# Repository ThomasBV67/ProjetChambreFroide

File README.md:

# ProjetChambreFroide
## Résumé du projet
Ce répertoire github contient tous les fichiers en lien avec notre projet. Ce projet se résume en un système de mesures et mise en mémoire de températures. Un module principal affiche les températures mesurée, garde en mémoire cette information et permet d'avoir accès à un historique des températures enregistrées. Un nombre variable de modules de mesures envoie des trames LoRa, contenant les températures mesurées par les capteurs de températures connectés à ceux-ci, au module principal.

## Dossiers
#### Électrique
Contient tout les fichiers et dossiers en lien avec la partie électronique du projet.

#### getAdressesCapteurs
Contient le projet arduino de test unitaire pour obtenir l'adresse des capteurs de températures.

#### LoRaSender
Contient le projet arduino de test unitaire d'envoi de trames LoRa.

#### ProgrammeModulesCentraux
Contient le projet arduino utilisé dans les modules de capteurs.

#### ProgrammePontLoRa
Contient le projet arduino utilisé pour faire le pont entre les trames LoRa et la connection série avec l'ordinateur.

#### testCapteurs
Contient le projet arduino utilisé pour tester le concept du projet (obtient les températures et envoi) du côté arduino.

#### TestPi
Contient le projet Visual Studio utilisé pour tester les fonctionnalitées de Windows 10 IoT Core.

#### TestRecieve
Contient le projet arduino utilisé pour tester la réception de trames LoRa.

#### TestSender
Contient le projet arduino utilisé pour tester l'envoi de trames LoRa.

#### UI_ChambreFroide_V1
Contient le projet principal Visual Studio.

## Fichiers
#### System.Data.SQLite.dll
Librairie utilisée pour utiliser SQLite dans le programme principal.

#### firstDraftUI_Projet.png
Idée de base pour l'affichage des températures

## Installation
#### Programme des cartes
Avant de mettre le programme spécifique à une carte, le bootloader doit etre installé. [Comment installer un bootloader](https://support.arduino.cc/hc/en-us/articles/360012048100-How-to-burn-the-bootloader-in-an-Arduino-Nano-using-an-Arduino-UNO)
Avant d'installer le bootloader, assurez vous que les jumpers JP101 et JP102 sont ouverts. Assurez vous de les fermer après son installation.
##### Module pont
Le programme du module pont est disponible sous /ProgrammePontLoRa/ProgrammePontLoRa.ino
Le fichier doit etre ouvert avec le logiciel Arduino.
Le programme est fait pour fonctionner avec les cartes "Module" disponibles sous /Électrique/Module Central/Module Central.pro
Compilez et envoyez le programme à la carte avec le logiciel Arduino
S'assurer que les syncWord des modules LoRa des modules correspondent (Disponibles entre 0x00 et 0xFF)
```c++
LoRa.setSyncWord(0x45);
```
##### Modules centraux
Le programme des modules centraux est disponible sous /ProgrammeModulesCentraux/ProgrammeModulesCentraux.ino
Le fichier doit etre ouvert avec le logiciel Arduino.
Le programme est fait pour fonctionner avec les cartes "Module" disponibles sous /Électrique/Module Central/Module Central.pro
Les cartes doivent etres numérotés. Il faut modifier la constante "NUM_MODULE" en commençant par 1 et en augmentant de 1 pour chaque module prévu sur le réseau
S'assurer que les syncWord des modules LoRa des modules correspondent (Disponibles entre 0x00 et 0xFF)
```c++
LoRa.setSyncWord(0x45);
```
Compilez et envoyez le programme à la carte avec le logiciel Arduino

#### Programme Principal
L'ensemble du programme principal est disponible sous /UI_ChambreFroide_V1/UI_ChambreFroide_V1/
Le projet s'ouvre avec visual studio. S'assurer que l'extensions "Développement .net Desktop" est installée dans VS

## Utilisation
### Commandes
Les commandes sont tout d'abord envoyés à partir d'un ordinateur vers le module de transmission qui se charge d'envoyer les informations de série vers LoRa et vice-versa. La commande est ensuite envoyée en LoRa et est reçue par tous les modules. Les modules vérifient ensuite l'information pour savoir si elle leur est destinée. Elle sera destinée à un seul module. Le module concerné traite ensuite la commande et récupère les informations demandés auprès des capteurs. Il renvois ensuite en un ou plusieurs messages dépendamment de la nature de la commande originale. Les données de réponses sont envoyées en LoRa et récupérés par le module de transmission qui les convertit en série et les renvoie à l'ordinateur. 

#### getAddr 
Commande permettant de lire l'adresse de tous les capteurs branchés à un module spécifié. 
Exemple d'utilisation: 1getAddr 

Le numéro du module interrogé est tout d'abord inséré suivi de la commande. La commande retourne  

Les adresses des différents capteurs qui y sont connectés sont envoyés, espacés par '#'

#### getTemp 
Commande retournant la température du thermomètre désiré.  

Exemple: 1getTemp-1 

Tout comme la première commande, le numéro de module est spécifié au départ. Le dernier chiffre correspond au numéro du thermomètre à lire. Le numéro correspond à la position d'arrivée de l'adresse dans la commande précédente.  

Le module interrogé renvoie une trame ressemblant à T#ADDR
Où T correspond à la température du capteur et ADDR à son addresse. L'addresse agit comme un checksum pour le programme principal.

### Principe de fonctionnement du programme principal
La prise de temprature par le programme principal fonctionne selon un principe d'action-réaction. Une premiere lecture est déclenchée par un timer, cette lecture est définie par l'envoi d'une commande "getTemp" et l'attente de sa réponse.
À partir de ce moment, deux actions sont possibles, soit la réponse du capteur est reçue, elle est donc validée et traitée. Soit un timer de timeout se déclenche, ce timer sert à protéger le programme contre les trames perdues. Lors de son déclenchement, le programme tentera de recontacter le capteur. Apres 4 essais échoués de suite, le programme abandonne, il marque donc le capteur comme déffectueux (La température est remplacé par "ERR" sur fond mauve.) et passe au prochain capteur.

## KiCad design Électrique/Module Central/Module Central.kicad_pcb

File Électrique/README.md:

# Électrique
## Dossiers
#### Module Central
Ce dossier contient le projet KiCad du PCB des modules de mesure de température.

## Fichiers
#### COM-13909.lib / COM-13909.step / MOD_COM-13909.kicad_mod
#### ProjetChambreFroide.bck / ProjetChambreFroide.dcm / ProjetChambreFroide.lib
Fichiers de librairies contenant entre autre l'emprunte du modem LoRa.

#### Commande de pièces.txt
Contient la liste des pièces à commander pour le PCB.

#### Liste d'achat.xlsx
Liste de pièces à commander et prix pour le montage de 10 PCB.

#### Liste de pièces.txt
Liste de toutes les pièces nécessaire pour les PCB (à commander et déjà au magasin).

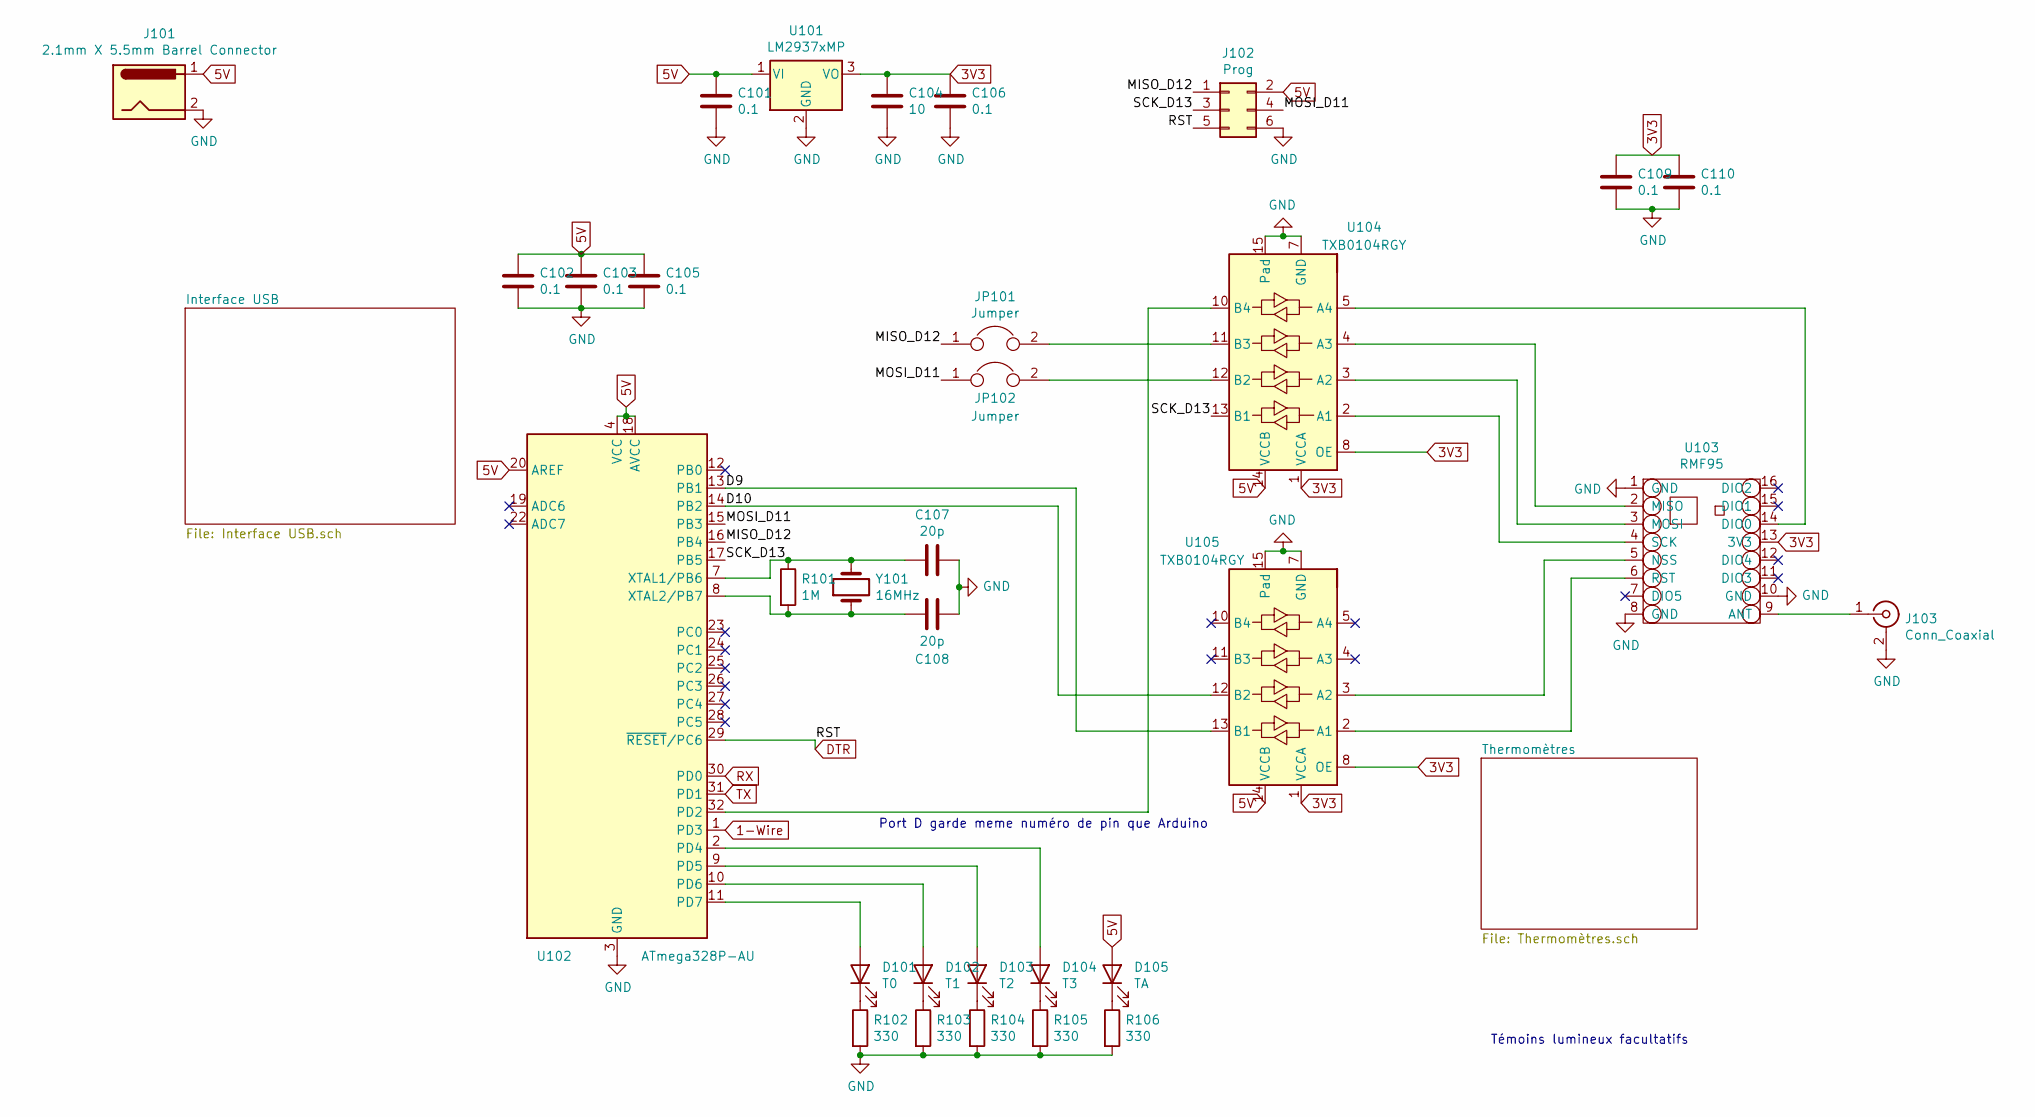
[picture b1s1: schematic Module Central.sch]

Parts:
C101, C102, C103, C105, C106, C109, C110: 0.1; C_0805_2012Metric
C104: 10; C_0805_2012Metric
C107, C108: 20p; C_0805_2012Metric
D101: T0; D_0805_2012Metric
D102: T1; D_0805_2012Metric
D103: T2; D_0805_2012Metric
D104: T3; D_0805_2012Metric
D105: TA; D_0805_2012Metric
J101: 2.1mm X 5.5mm Barrel Connector; BarrelJack_Horizontal
J102: Prog; PinSocket_2x03_P2.54mm_Vertical
J103: Conn_Coaxial; SMA_Molex_73251-2200_Horizontal
JP101, JP102: Jumper; SolderJumper-2_P1.3mm_Open_Pad1.0x1.5mm
R101: 1M; R_0805_2012Metric
R102, R103, R104, R105, R106: 330; R_0805_2012Metric
U101: LM2937xMP; SOT-223-3_TabPin2
U102: ATmega328P-AU; TQFP-32_7x7mm_P0.8mm
U103: RMF95; MOD_COM-13909
U104, U105: TXB0104RGY; Texas_S-PVQFN-N14
Y101: 16MHz; Crystal_SMD_HC49-SD

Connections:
1-Wire: U102.1 (PD3); also elsewhere on the board
3V3: C104.1, C106.1, C109.1, C110.1, U101.3 (VO), U103.13 (3V3), U104.1 (VCCA), U104.8 (OE), U105.1 (VCCA), U105.8 (OE); also elsewhere on the board
5V: C101.1, C102.1, C103.1, C105.1, D105.2 (A), J101.1, J102.2, U101.1 (VI), U102.4 (VCC), U102.6 (VCC), U102.18 (AVCC), U102.20 (AREF), U104.14 (VCCB), U105.14 (VCCB); also elsewhere on the board
/D9: U102.13 (PB1), U105.13 (B1)
/D10: U102.14 (PB2), U105.12 (B2)
/MISO_D12: J102.1, JP101.1, U102.16 (PB4)
/MOSI_D11: J102.4, JP102.1, U102.15 (PB3)
/SCK_D13: J102.3, U102.17 (PB5), U104.13 (B1)
DTR: J102.5, U102.29 (~RESET~/PC6); also elsewhere on the board
GND: C101.2, C102.2, C103.2, C104.2, C105.2, C106.2, C107.1, C108.1, C109.2, C110.2, J101.2, J102.6, J103.2 (Ext), R102.2, R103.2, R104.2, R105.2, R106.2, U101.2 (GND), U102.3 (GND), U102.5 (GND), U102.21 (GND), U103.1 (GND), U103.8 (GND), U103.10 (GND), U104.7 (GND), U104.15 (Pad), U105.7 (GND), U105.15 (Pad); also elsewhere on the board
unnamed: C107.2, R101.1, U102.7 (XTAL1/PB6), Y101.2
unnamed: C108.2, R101.2, U102.8 (XTAL2/PB7), Y101.1
unnamed: D101.1 (K), R102.1
unnamed: D101.2 (A), U102.11 (PD7)
unnamed: D102.1 (K), R103.1
unnamed: D102.2 (A), U102.10 (PD6)
unnamed: D103.1 (K), R104.1
unnamed: D103.2 (A), U102.9 (PD5)
unnamed: D104.1 (K), R105.1
unnamed: D104.2 (A), U102.2 (PD4)
unnamed: D105.1 (K), R106.1
unnamed: J103.1 (In), U103.9 (ANT)
unnamed: JP101.2, U104.11 (B3)
unnamed: JP102.2, U104.12 (B2)
unnamed: U102.32 (PD2), U104.10 (B4)
unnamed: U103.2 (MISO), U104.4 (A3)
unnamed: U103.3 (MOSI), U104.3 (A2)
unnamed: U103.4 (SCK), U104.2 (A1)
unnamed: U103.5 (NSS), U105.3 (A2)
unnamed: U103.6 (RST), U105.2 (A1)
unnamed: U103.14 (DIO0), U104.5 (A4)
RX: U102.30 (PD0); also elsewhere on the board
TX: U102.31 (PD1); also elsewhere on the board

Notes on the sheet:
Port D garde meme numéro de pin que Arduino
Témoins lumineux facultatifs

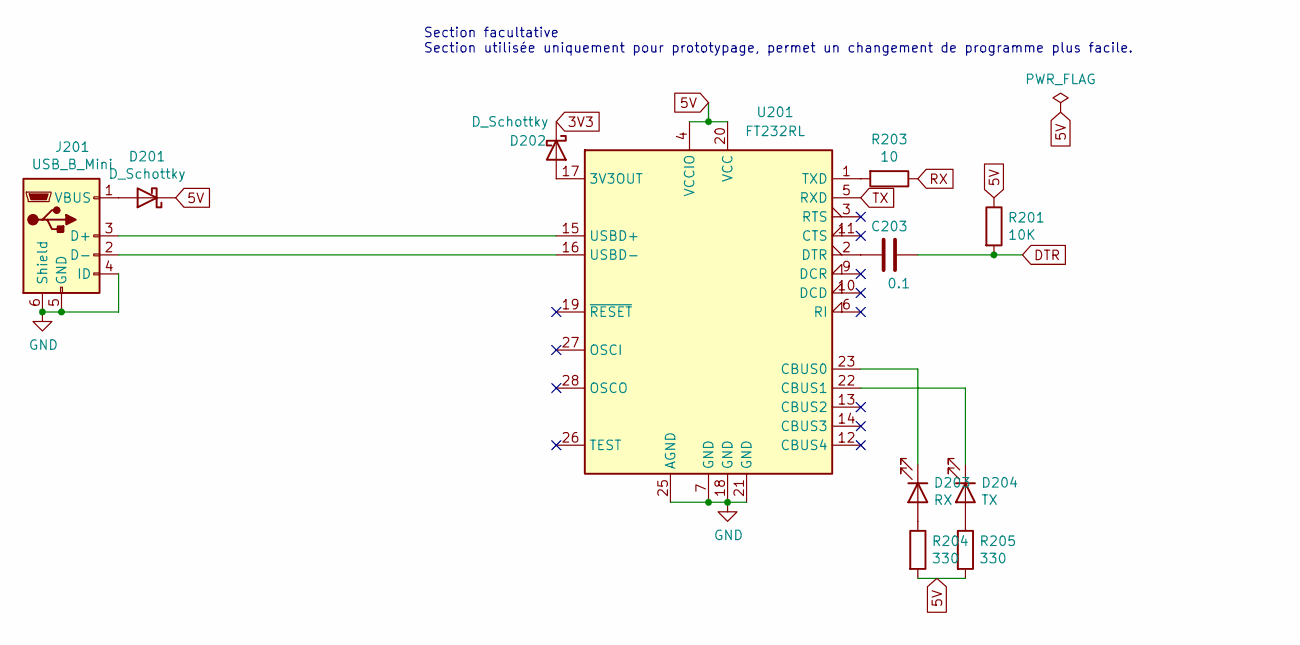
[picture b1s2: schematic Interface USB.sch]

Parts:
C203: 0.1; C_0805_2012Metric
D201, D202: D_Schottky; D_0805_2012Metric
D203: RX; D_0805_2012Metric
D204: TX; D_0805_2012Metric
J201: USB_B_Mini; USB_Mini-B_Lumberg_2486_01_Horizontal
R201: 10K; R_0805_2012Metric
R203: 10; R_0805_2012Metric
R204, R205: 330; R_0805_2012Metric
U201: FT232RL; SSOP-28_5.3x10.2mm_P0.65mm

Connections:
3V3: D202.1 (K); also elsewhere on the board
5V: D201.1 (K), R201.1, R204.2, R205.2, U201.4 (VCCIO), U201.20 (VCC); also elsewhere on the board
DTR: C203.1, R201.2; also elsewhere on the board
GND: J201.4 (ID), J201.5 (GND), J201.6 (Shield), U201.7 (GND), U201.18 (GND), U201.21 (GND), U201.25 (AGND); also elsewhere on the board
unnamed: C203.2, U201.2 (DTR)
unnamed: D201.2 (A), J201.1 (VBUS)
unnamed: D202.2 (A), U201.17 (3V3OUT)
unnamed: D203.1 (K), U201.23 (CBUS0)
unnamed: D203.2 (A), R204.1
unnamed: D204.1 (K), U201.22 (CBUS1)
unnamed: D204.2 (A), R205.1
unnamed: J201.2 (D-), U201.16 (USBD-)
unnamed: J201.3 (D+), U201.15 (USBD+)
unnamed: R203.2, U201.1 (TXD)
RX: R203.1; also elsewhere on the board
TX: U201.5 (RXD); also elsewhere on the board

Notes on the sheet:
Section facultative Section utilisée uniquement pour prototypage, permet un changement de programme plus facile.

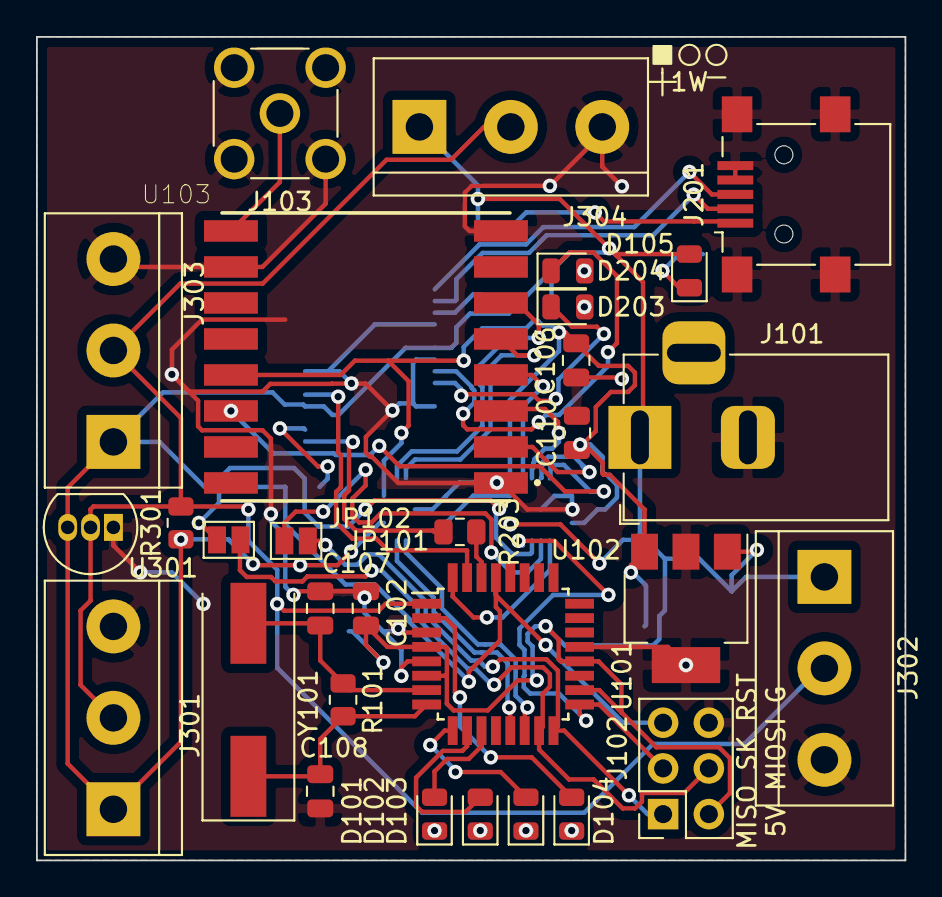
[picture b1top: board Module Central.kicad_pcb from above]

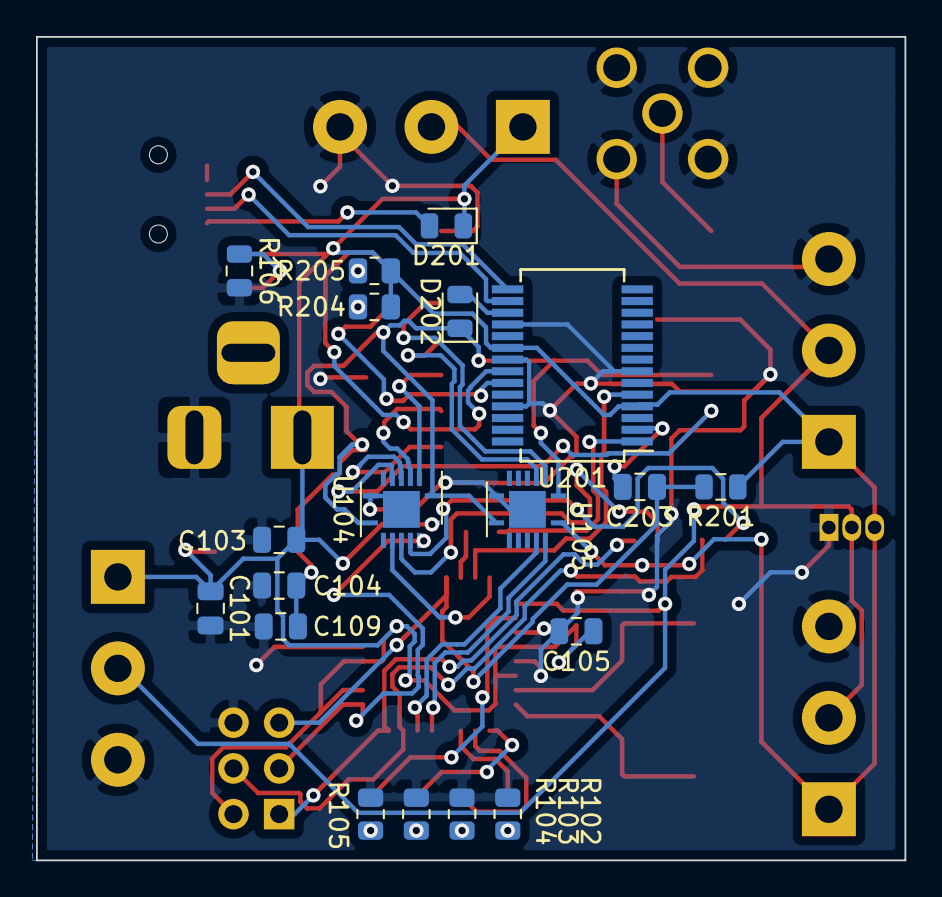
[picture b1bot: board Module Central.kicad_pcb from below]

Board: 2 copper layers, 48.2 x 45.8 mm, 49 parts (19 on the bottom side), 43 nets.

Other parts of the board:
J301: Borne 0; TerminalBlock_bornier-3_P5.08mm
J302: Borne 1; TerminalBlock_bornier-3_P5.08mm
J303: Borne 2; TerminalBlock_bornier-3_P5.08mm
J304: Borne 3; TerminalBlock_bornier-3_P5.08mm
R301: 4.7K; R_0805_2012Metric
U301: DS18B20; TO-92_Inline

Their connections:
1-Wire: J301.2, J302.2, J303.2, J304.2, R301.2, U301.2; also elsewhere on the board
5V: J301.1, J302.1, J303.1, J304.1, R301.1, U301.3; also elsewhere on the board
GND: J301.3, J302.3, J303.3, J304.3, U301.1; also elsewhere on the board

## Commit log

2021-01-19 Ajout des fichiers déjà créés au repo
2021-01-19 Ajout du programme de test unitaire receveur LoRa
2021-01-25 Ajout et modification des programmes de test
2021-01-25 Ajout du schéma électrique
2021-01-25 Modification des programmes de test unitaires
2021-01-25 Fichiers inutiles retirés
2021-01-25 MAJ liste pieces
2021-01-26 Ajout d'un programme de test pour windows 10 iot core
2021-01-26 Réparation fichiers Kicad
2021-01-26 Ajout Btn Elian
2021-01-26 Modification du bouton
2021-01-26 Ajout Lib LoRa
2021-01-26 Remise a zero du programme de l'interface graphique
2021-01-26 Ajout de librairies pour graphiques au programme de test du Pi
2021-01-27 Ajout de l'exemple de menu principal- Élian
2021-01-28 Version ajustée pour un écran 1024x600
2021-01-28 Ajout Page configuration
2021-02-01 Ajout de fichiers
2021-02-01 Ajout d'un projet VS pour l'interface du système
2021-02-01 Rien
2021-02-01 Modification du format des fenêtres de l'interface
2021-02-01 Modification des fenêtres
2021-02-01 Ajout de la page de selection
2021-02-01 Page principale UI et Gerber générés
2021-02-01 Changement de fichier pour le code precedent
2021-02-02 Ajout de boutons pour changer de form
2021-02-02 Ajout DEL témoin
2021-02-02 Modification de l'ouverture de nouveaux forms
2021-02-02 Définition des tableaux qui contiennent les temps.
2021-02-02 Je sais plus
2021-02-02 Ajout début de database
2021-02-02 Début de fonction de la DB
2021-02-02 Ajout des programmes des microcontroleurs
2021-02-02 Version sommaire de la page de configuration
2021-02-02 DataBase un minimum foctionelle
2021-02-03 Ajout de commentaires dans le programme d'UI
2021-02-03 Ajout de boutons retour pour chaque for
2021-02-04 Wassup
2021-02-05 Ajout de la configuration du port série
2021-02-08 Ajout de nugget et début de remaniment du transfer de données à la DB
2021-02-08 Sauvegarde du projet
2021-02-08 something
2021-02-08 Progression de la connection a la db
2021-02-08 Début de decouverte de réseau
2021-02-08 DB Fonctionnelle
2021-02-08 qq chose
2021-02-08 Ajout des fonctions GetUnsetCapteurs et GetSetCapteurs
2021-02-08 Base de decouverte reseau
2021-02-08 Ajout de commentaires, deletion de code innutile
2021-02-08 Traitement de l'entrée série
2021-02-08 Auto stash before merge of "main" and "origin/main"
2021-02-08 Ecriture dans la db fonctionelle
2021-02-08 Découverte réseau
2021-02-09 Ajout de fonction pour ajouter et modifier des capteurs dans la database
2021-02-09 fonction scan module
2021-02-09 Choix de capteur pour l'historique
2021-02-09 Découverte du reseau V1
2021-02-09 Ajout de commentaires
2021-02-09 Autres commentaires
2021-02-09 Ajout de la classe de température
2021-02-10 Ajout de coms
2021-02-10 Lecture des temps
2021-02-10 Ajout de la fonction pour ajouter des temps a la db
2021-02-10 Essai d'implémentation de la sauvegarde des temps
2021-02-11 Correction de bugs de prise de température
2021-02-12 Correction de bugs variés et implémentation de protection contre les données de températures invalides
2021-02-12 Commentaire
2021-02-13 Ajout de marqueurs de test pour vérifier la fiabilité du programme
2021-02-13 Correction bug mineur
2021-02-13 Correction bug majeur
2021-02-15 Retirer tous les fichiers qui ne servent pas et ajout de readme
2021-02-15 Retirer plus de fichiers innutiles
2021-02-16 Ajout de commentaires et modification des readme
2021-02-16 Changement baudRate
2021-02-16 Changement baudRate par défaut
2021-02-16 Finition des readme et ajout de commentaires
2021-02-17 Modification du mode de configuration
2021-02-22 Début de la fenêtre de modification de capteurs
2021-02-23 Progression de la modif de capteurs
2021-02-23 Autre progression
2021-02-23 Clavier visuel affiche
2021-02-24 Correction des erreurs sur le schéma
2021-02-24 Modification PCB prete à faire
2021-02-24 Progression de l'UI
2021-02-24 oups
2021-02-24 PCB modifié
2021-03-09 Début de la création du clavier visuel
2021-03-09 Essai d'enregistrement dans la db
2021-03-09 Début de l'implémentation d'un affichage d'historique
2021-03-09 BugFix
2021-03-09 Création du clavier visuel
2021-03-09 Ajout de code de test pour afficher des données de la db
2021-03-09 Implantation du clavier dans FormModifCapteur
2021-03-09 Modif de la requete sql
2021-03-09 bug fix, i guess
2021-03-09 Clavier fonctionnel
2021-03-09 Regen
2021-03-09 Clean-Build
2021-03-09 4 tentatives
2021-03-09 Revert "Merge remote-tracking branch 'origin/main' into main"
    This reverts commit aadcd3b6d0f76c3d5354ceba3bde9bde92245503, reversing
    changes made to e8bdfc570f9a8634e49c325ff97007f6658bfbaa.
2021-03-09 4 tentatives?
2021-03-10 Correction bug
2021-03-10 Modification du layout de boutons de config et de temp actuelles
2021-03-10 Ajustement taille police config
2021-03-10 Ajustement des tailles de colonnes de la config
2021-03-12 Ajout des controles pour changer de page
2021-03-15 Update du formatage de texte
2021-03-15 Update du formatage de texte 2
2021-03-15 Modification PCB
    Changement des Level shifters pour des pieces disponibles
2021-03-15 Changement des info de debug de la page principale
2021-03-15 Changement des info de debug de la page principale 2
2021-03-15 Réduction du temps entre les prises de données
2021-03-15 Modif PCB en cours
2021-03-15 Bugfix de plantage quand erreur critique
2021-03-15 PCB Avec 2x 4Channel LevelShifters
2021-03-16 Meilleure gestion des erreurs
2021-03-16 Query filtrée par temps fonctionnelle et update de capteur par address
2021-03-16 Debut de sauvegarde de config
2021-03-16 Sauvegarde des parametres
2021-03-16 Ajout d'une fonction pour retirer des capteurs de la database
2021-03-16 Autoscroll FormConfig
2021-03-16 Ajout d'un nugget package pour les graphiques
2021-03-16 Ajout de la fonction de suppression de capteur
2021-03-16 Ajout fonction Ping
2021-03-16 Recompilation
2021-03-17 Plus de capteurs fictifs
2021-03-17 Bug dans le path des fichiers
2021-03-17 Ajout de bouton arret / depart et demarrage auto
2021-03-17 Programme compilé et temps d'attente adapté aux tests
2021-03-17 Small bugfix
2021-03-22 Bugfix && improved stability
2021-03-22 Bug fix
2021-03-23 Ajout des Watchdog
2021-03-23 Fuck le README
2021-03-23 Changement de l'acces à l'historique
2021-03-24 Fonction de graphiques multi-lignes basiques
2021-03-29 MAJ de la liste d'achats pour la carte
    Liste d'achat complète des pièces du PCB
2021-03-31 MAJ liste matériel
2021-03-31 Ajout de fonctionnalitées au graphique
2021-03-31 Ajout de labels pour les erreurs du module 3
2021-03-31 Build
2021-04-06 Preparation pour demo
2021-04-06 J' "aime" le README
2021-04-06 Num module ajusté
2021-04-06 Ajout de fonctionnalitées au graphique et cleanup de bugs
2021-04-07 Ajout d'entêtes de fichiers
2021-04-07 Summary modifCapteurs.cs ajouté
2021-04-12 Push travail maison (graphique)
2021-04-13 Graphique complet
2021-04-13 Choix du temps du graph
2021-04-17 Ajout des modèles 3d des supports pour les cartes et l'écran
2021-04-18 Ajustement des tolérances
2021-04-19 Préparation à l'installation client du programme principal
2021-04-20 System fonctionnel
2021-04-20 Test timestamps en unix
2021-04-20 test request sql unix
2021-04-20 Unix time fonctionnel
2021-04-20 Clean-up du code + Ajout de comms
2021-04-21 Build pour push stratos
2021-04-23 Ajout d'une protection au cas ou le modem lora ne répond plus
2021-04-26 Ajout du programme chez le client pour pré démo
2021-04-28 push initial branch
2021-04-28 push du code de test
2021-04-28 Nouvelle logique de gestion de données fonctionelle
2021-04-28 Ajout Archive
2021-04-28 Bux fix
2021-04-28 Bugfix 2
